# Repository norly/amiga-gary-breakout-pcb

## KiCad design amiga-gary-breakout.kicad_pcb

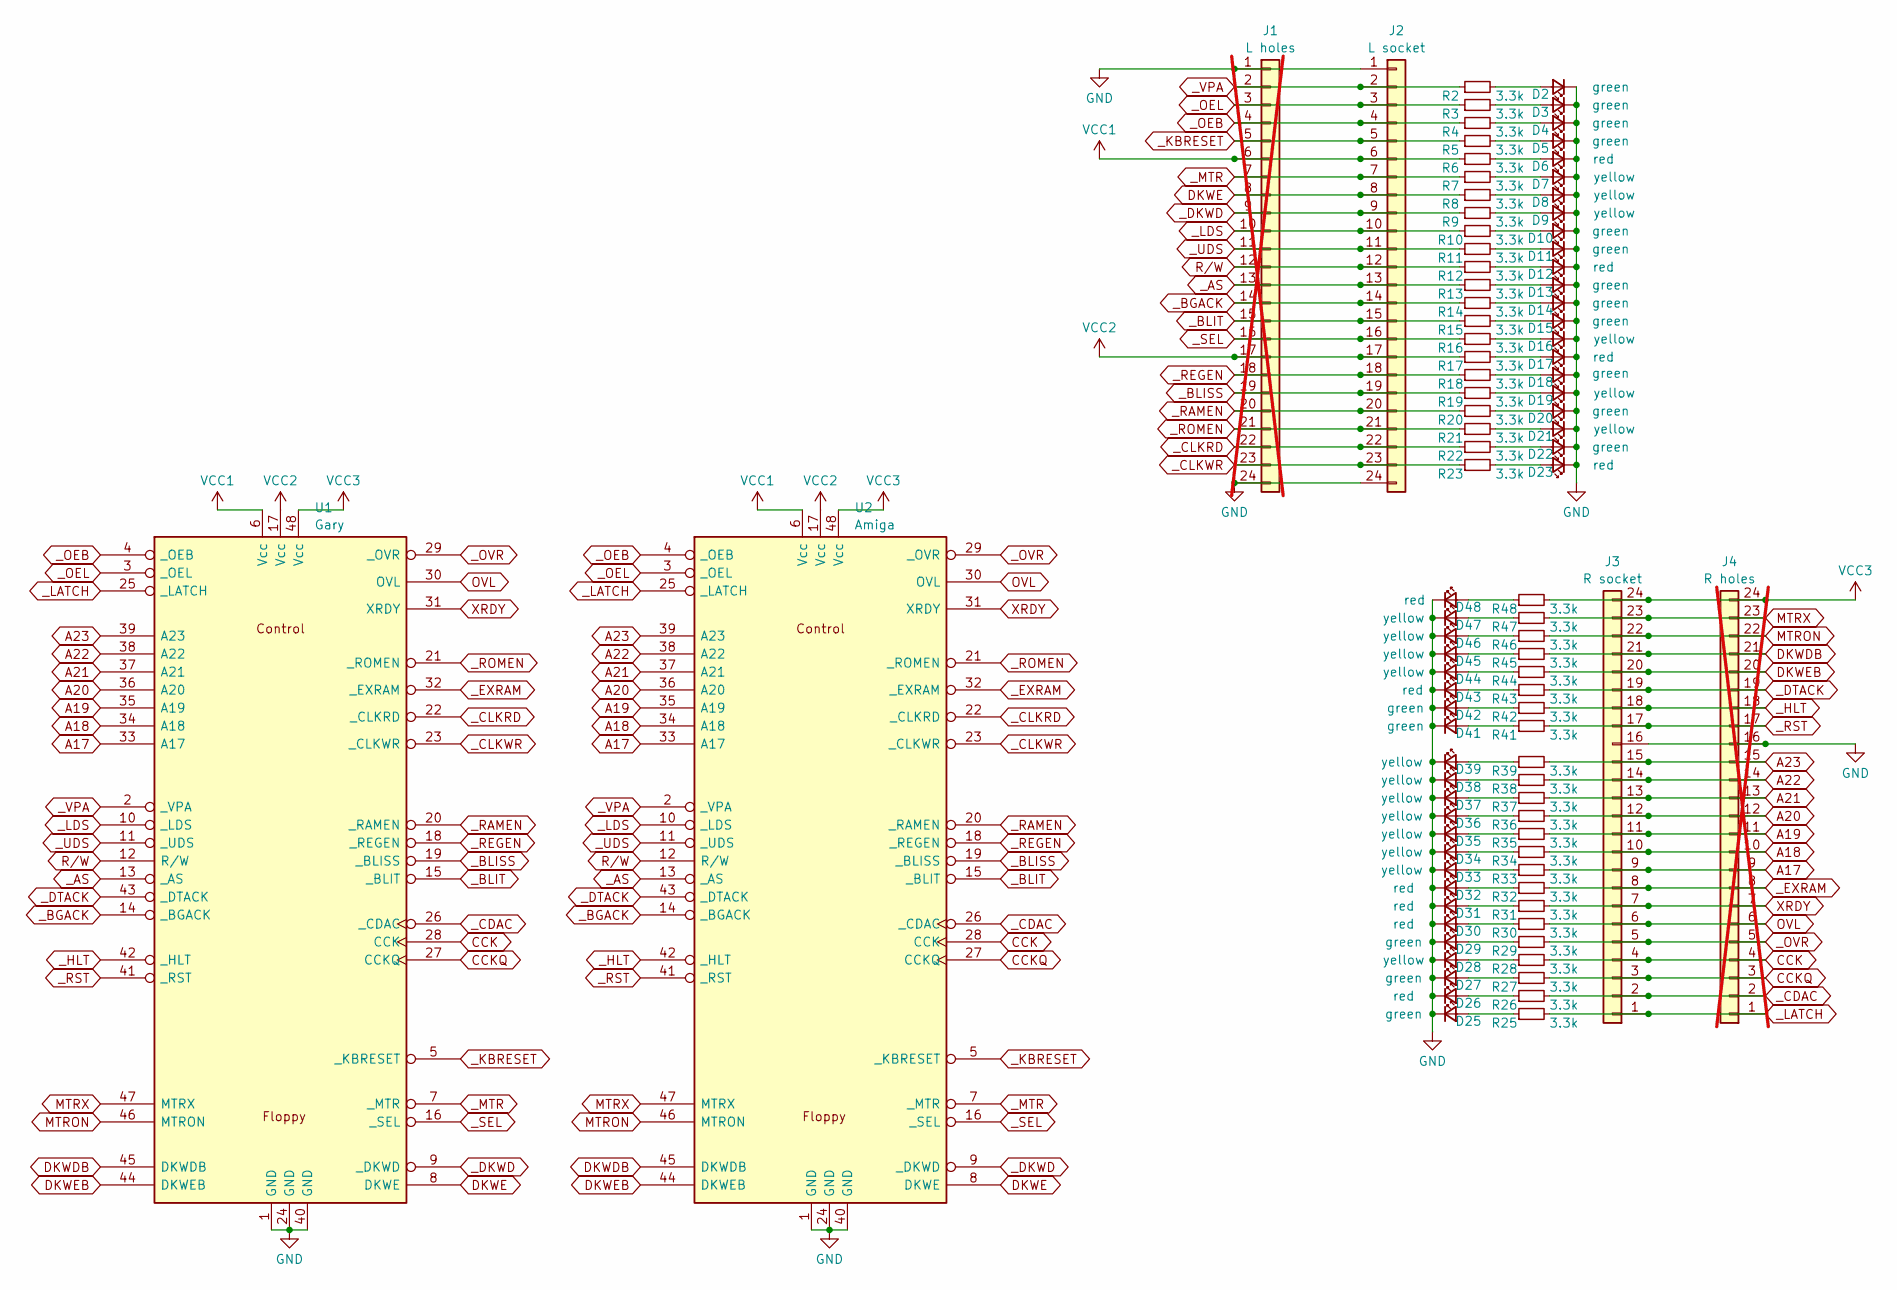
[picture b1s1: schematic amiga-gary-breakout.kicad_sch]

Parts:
D2, D3, D4, D5, D10, D11, D13, D14, D15, D18, D20, D22, D25, D27, D29, D41, D42: green; LED_0805_2012Metric_Pad1.15x1.40mm_HandSolder; JLCPCB C2297
D6, D12, D17, D23, D26, D30, D31, D32, D43, D48: red; LED_0805_2012Metric_Pad1.15x1.40mm_HandSolder; JLCPCB C84256
D7, D8, D9, D16, D19, D21, D28, D33, D34, D35, D36, D37, D38, D39, D44, D45, D46, D47: yellow; LED_0805_2012Metric_Pad1.15x1.40mm_HandSolder; JLCPCB C2296
J1: L holes; PinHeader_1x24_P2.54mm_Vertical; not fitted
J2: L socket; PinSocket_1x24_P2.54mm_Vertical; LCSC C41376163
J3: R socket; PinSocket_1x24_P2.54mm_Vertical; LCSC C41376163
J4: R holes; PinHeader_1x24_P2.54mm_Vertical; not fitted
R2, R3, R4, R5, R6, R7, R8, R9, R10, R11, R12, R13, R14, R15, R16, R17, R18, R19, R20, R21, R22, R23, R25, R26, R27, R28, R29, R30, R31, R32, R33, R34, R35, R36, R37, R38, R39, R41, R42, R43, R44, R45, R46, R47, R48: 3.3k; R_0603_1608Metric_Pad0.98x0.95mm_HandSolder; JLCPCB C22978
U1: Gary; DIP-48_W15.24mm_Socket_LongPads; LCSC C72120
U2: Amiga; DIP-48_W15.24mm_Socket_LongPads; LCSC C72120

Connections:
A17: J3.9, J4.9, R33.2, U1.33 (A17), U2.33 (A17)
A18: J3.10, J4.10, R34.2, U1.34 (A18), U2.34 (A18)
A19: J3.11, J4.11, R35.2, U1.35 (A19), U2.35 (A19)
A20: J3.12, J4.12, R36.2, U1.36 (A20), U2.36 (A20)
A21: J3.13, J4.13, R37.2, U1.37 (A21), U2.37 (A21)
A22: J3.14, J4.14, R38.2, U1.38 (A22), U2.38 (A22)
A23: J3.15, J4.15, R39.2, U1.39 (A23), U2.39 (A23)
CCK: J3.4, J4.4, R28.2, U1.28 (CCK), U2.28 (CCK)
CCKQ: J3.3, J4.3, R27.2, U1.27 (CCKQ), U2.27 (CCKQ)
DKWDB: J3.21, J4.21, R45.2, U1.45 (DKWDB), U2.45 (DKWDB)
DKWE: J1.8, J2.8, R8.1, U1.8 (DKWE), U2.8 (DKWE)
DKWEB: J3.20, J4.20, R44.2, U1.44 (DKWEB), U2.44 (DKWEB)
GND: D2.1 (K), D3.1 (K), D4.1 (K), D5.1 (K), D6.1 (K), D7.1 (K), D8.1 (K), D9.1 (K), D10.1 (K), D11.1 (K), D12.1 (K), D13.1 (K), D14.1 (K), D15.1 (K), D16.1 (K), D17.1 (K), D18.1 (K), D19.1 (K), D20.1 (K), D21.1 (K), D22.1 (K), D23.1 (K), D25.1 (K), D26.1 (K), D27.1 (K), D28.1 (K), D29.1 (K), D30.1 (K), D31.1 (K), D32.1 (K), D33.1 (K), D34.1 (K), D35.1 (K), D36.1 (K), D37.1 (K), D38.1 (K), D39.1 (K), D41.1 (K), D42.1 (K), D43.1 (K), D44.1 (K), D45.1 (K), D46.1 (K), D47.1 (K), D48.1 (K), J1.1, J1.24, J2.1, J2.24, J3.16, J4.16, U1.1 (GND), U1.24 (GND), U1.40 (GND), U2.1 (GND), U2.24 (GND), U2.40 (GND)
MTRON: J3.22, J4.22, R46.2, U1.46 (MTRON), U2.46 (MTRON)
MTRX: J3.23, J4.23, R47.2, U1.47 (MTRX), U2.47 (MTRX)
unnamed: D2.2 (A), R2.2
unnamed: D3.2 (A), R3.2
unnamed: D4.2 (A), R4.2
unnamed: D5.2 (A), R5.2
unnamed: D6.2 (A), R6.2
unnamed: D7.2 (A), R7.2
unnamed: D8.2 (A), R8.2
unnamed: D9.2 (A), R9.2
unnamed: D10.2 (A), R10.2
unnamed: D11.2 (A), R11.2
unnamed: D12.2 (A), R12.2
unnamed: D13.2 (A), R13.2
unnamed: D14.2 (A), R14.2
unnamed: D15.2 (A), R15.2
unnamed: D16.2 (A), R16.2
unnamed: D17.2 (A), R17.2
unnamed: D18.2 (A), R18.2
unnamed: D19.2 (A), R19.2
unnamed: D20.2 (A), R20.2
unnamed: D21.2 (A), R21.2
unnamed: D22.2 (A), R22.2
unnamed: D23.2 (A), R23.2
unnamed: D25.2 (A), R25.1
unnamed: D26.2 (A), R26.1
unnamed: D27.2 (A), R27.1
unnamed: D28.2 (A), R28.1
unnamed: D29.2 (A), R29.1
unnamed: D30.2 (A), R30.1
unnamed: D31.2 (A), R31.1
unnamed: D32.2 (A), R32.1
unnamed: D33.2 (A), R33.1
unnamed: D34.2 (A), R34.1
unnamed: D35.2 (A), R35.1
unnamed: D36.2 (A), R36.1
unnamed: D37.2 (A), R37.1
unnamed: D38.2 (A), R38.1
unnamed: D39.2 (A), R39.1
unnamed: D41.2 (A), R41.1
unnamed: D42.2 (A), R42.1
unnamed: D43.2 (A), R43.1
unnamed: D44.2 (A), R44.1
unnamed: D45.2 (A), R45.1
unnamed: D46.2 (A), R46.1
unnamed: D47.2 (A), R47.1
unnamed: D48.2 (A), R48.1
OVL: J3.6, J4.6, R30.2, U1.30 (OVL), U2.30 (OVL)
R/W: J1.12, J2.12, R12.1, U1.12 (R/W), U2.12 (R/W)
VCC1: J1.6, J2.6, R6.1, U1.6 (Vcc), U2.6 (Vcc)
VCC2: J1.17, J2.17, R17.1, U1.17 (Vcc), U2.17 (Vcc)
VCC3: J3.24, J4.24, R48.2, U1.48 (Vcc), U2.48 (Vcc)
XRDY: J3.7, J4.7, R31.2, U1.31 (XRDY), U2.31 (XRDY)
_AS: J1.13, J2.13, R13.1, U1.13 (_AS), U2.13 (_AS)
_BGACK: J1.14, J2.14, R14.1, U1.14 (_BGACK), U2.14 (_BGACK)
_BLISS: J1.19, J2.19, R19.1, U1.19 (_BLISS), U2.19 (_BLISS)
_BLIT: J1.15, J2.15, R15.1, U1.15 (_BLIT), U2.15 (_BLIT)
_CDAC: J3.2, J4.2, R26.2, U1.26 (_CDAC), U2.26 (_CDAC)
_CLKRD: J1.22, J2.22, R22.1, U1.22 (_CLKRD), U2.22 (_CLKRD)
_CLKWR: J1.23, J2.23, R23.1, U1.23 (_CLKWR), U2.23 (_CLKWR)
_DKWD: J1.9, J2.9, R9.1, U1.9 (_DKWD), U2.9 (_DKWD)
_DTACK: J3.19, J4.19, R43.2, U1.43 (_DTACK), U2.43 (_DTACK)
_EXRAM: J3.8, J4.8, R32.2, U1.32 (_EXRAM), U2.32 (_EXRAM)
_HLT: J3.18, J4.18, R42.2, U1.42 (_HLT), U2.42 (_HLT)
_KBRESET: J1.5, J2.5, R5.1, U1.5 (_KBRESET), U2.5 (_KBRESET)
_LATCH: J3.1, J4.1, R25.2, U1.25 (_LATCH), U2.25 (_LATCH)
_LDS: J1.10, J2.10, R10.1, U1.10 (_LDS), U2.10 (_LDS)
_MTR: J1.7, J2.7, R7.1, U1.7 (_MTR), U2.7 (_MTR)
_OEB: J1.4, J2.4, R4.1, U1.4 (_OEB), U2.4 (_OEB)
_OEL: J1.3, J2.3, R3.1, U1.3 (_OEL), U2.3 (_OEL)
_OVR: J3.5, J4.5, R29.2, U1.29 (_OVR), U2.29 (_OVR)
_RAMEN: J1.20, J2.20, R20.1, U1.20 (_RAMEN), U2.20 (_RAMEN)
_REGEN: J1.18, J2.18, R18.1, U1.18 (_REGEN), U2.18 (_REGEN)
_ROMEN: J1.21, J2.21, R21.1, U1.21 (_ROMEN), U2.21 (_ROMEN)
_RST: J3.17, J4.17, R41.2, U1.41 (_RST), U2.41 (_RST)
_SEL: J1.16, J2.16, R16.1, U1.16 (_SEL), U2.16 (_SEL)
_UDS: J1.11, J2.11, R11.1, U1.11 (_UDS), U2.11 (_UDS)
_VPA: J1.2, J2.2, R2.1, U1.2 (_VPA), U2.2 (_VPA)

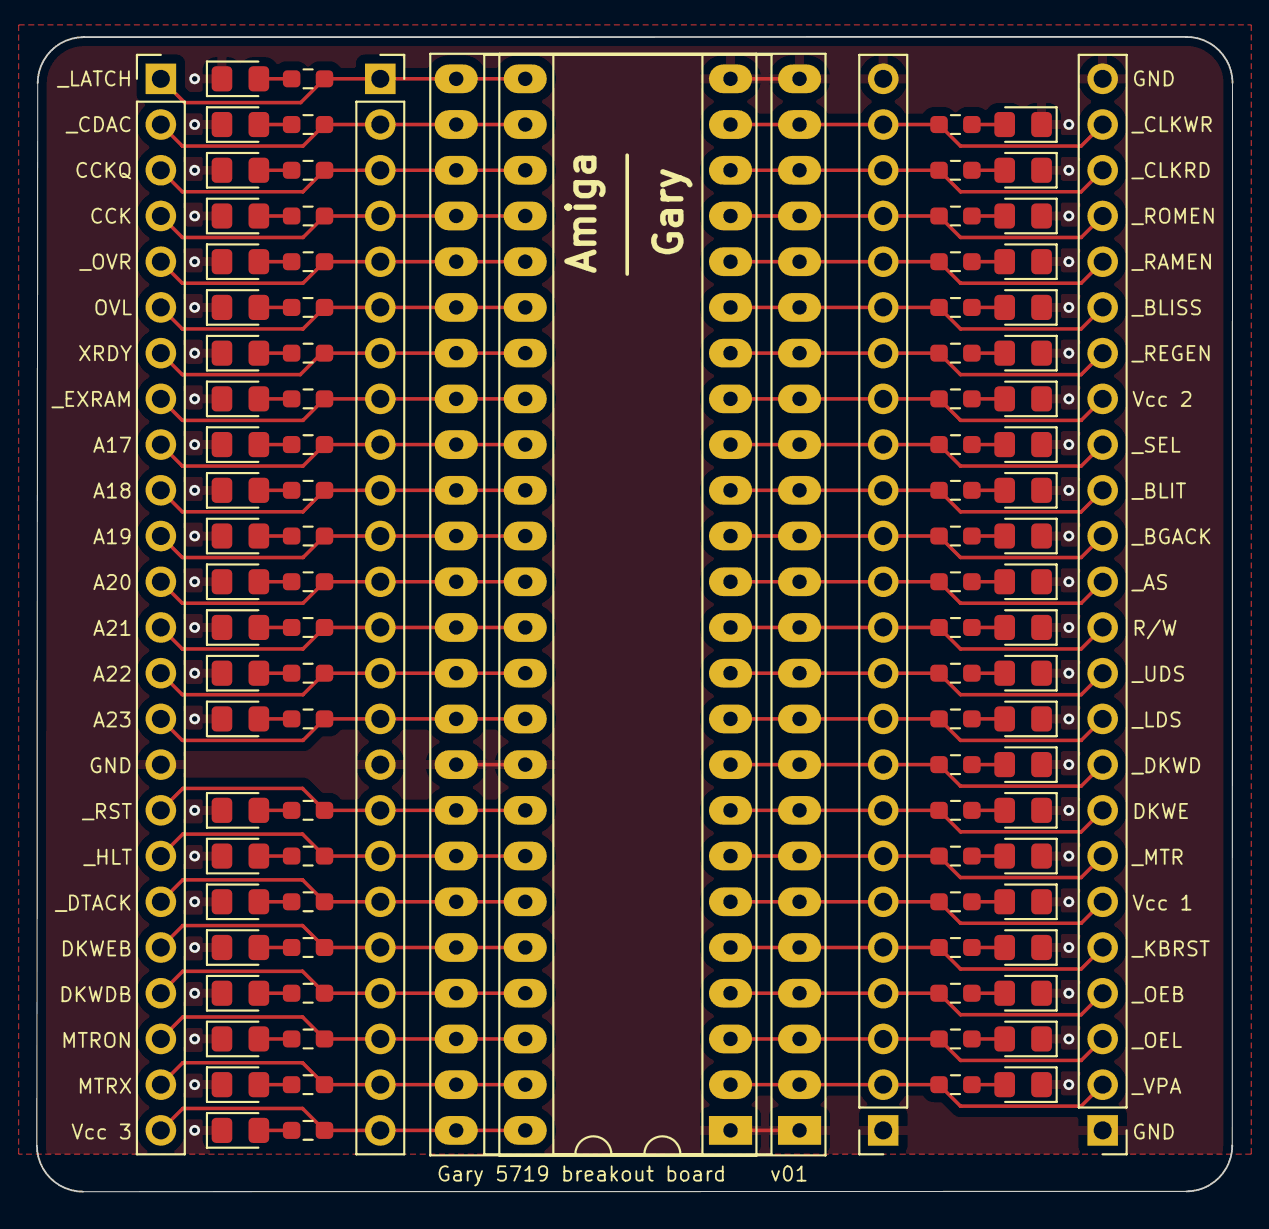
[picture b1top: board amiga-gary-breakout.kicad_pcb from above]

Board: 2 copper layers, 66.4 x 64.2 mm, 96 parts (0 on the bottom side), 91 nets.

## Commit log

2024-09-25 Add .gitignore
2024-11-02 LICENSE: CC0
